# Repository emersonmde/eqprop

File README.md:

# Analog equilibrium propagation — XOR prototype B.1

A two-hidden-node analog resistive network for learning XOR through equilibrium propagation. The circuit settles physically; a classic 5 V Arduino Nano will measure equilibria and update sixteen programmable resistances. **The PCB is routed and checked; Nano firmware and physical validation are not yet implemented/completed.**

Start every new session with [project state and next steps](docs/project-state.md). It records what exists, what remains, and where to find the design, fabrication, programming and debugging instructions.

## Working files

- [Native KiCad project](cad/eqprop-xor/eqprop-xor.kicad_pro), including its child sheets and local libraries.
- [Design rationale and datasheets](docs/design.md), [component/pin tables](docs/kicad/00-overview.md), [preferred-parts BOM](docs/bom-pcbway.csv).
- [PCBWay fabrication and assembly](docs/fabrication.md).
- [Nano firmware contract](docs/firmware.md), [bench bring-up](docs/bring-up.md), [demo operation](docs/operation.md).
- [Engineering review](docs/ee-review.md), [validation evidence](docs/validation/).

## Simulation and release checks

From the repository root, using Python 3 and a virtual environment:

```sh
python3 -m venv .venv
source .venv/bin/activate
python -m pip install -r sim/requirements.txt
PYTHONPATH=sim python -m pytest sim/tests -q
PYTHONPATH=sim python -m eqprop.xor
python tools/generate_bom.py
python tools/export_manufacturing.py
```

Install ngspice for the SPICE tests; those tests skip when it is absent, so skipped tests do not constitute a complete release check. KiCad 9's `kicad-cli` is required for manufacturing export. The script discovers PATH or the standard macOS install; `--kicad-cli` can specify another executable. Generated fabrication files go in ignored `build/manufacturing/`. Save the exact approved release with the PCBWay order records when an order is placed.

The regression suite checks KCL, gradients, training, quantization, SPICE behavior and BOM consistency. These are retained because later hardware/firmware changes need them. Nominal DC models do not prove stability, noise, component spread or online finite-tap learning.

## Papers and Attribution

This project is a from-scratch implementation of techniques described in the following papers. No code was reused from any existing repository.

**Core algorithm:**
- Scellier & Bengio, ["Equilibrium Propagation: Bridging the Gap Between Energy-Based Models and Backpropagation"](https://arxiv.org/abs/1602.05179) (Frontiers in Computational Neuroscience, 2017) — the equilibrium propagation framework: free-phase settling, nudge-phase perturbation, and gradient extraction from energy differences.

**Analog hardware formulation:**
- Kendall et al., ["Training End-to-End Analog Neural Networks with Equilibrium Propagation"](https://arxiv.org/abs/2006.01981) (2020) — extends EqProp to nonlinear resistive networks. This project uses their conductance-space gradient formula (Theorem 1: `dC/dG = (dV_nudge² - dV_free²) / (2β)`), their proof that antiparallel diode pairs are valid EqProp nonlinear elements (Theorem 2), and their XOR demonstration architecture (Figure 3, Appendix D.2) as a starting point. The complementary-input encoding and digital-weight-update pattern also follow their approach.

**Symmetric nudging:**
- Laborieux et al., ["Scaling Equilibrium Propagation to Deep ConvNets by Drastically Reducing its Computational Cost"](https://arxiv.org/abs/2006.03824) (ICLR 2021) — the symmetric nudge variant (both +β and -β) used in the training loop to cancel gradient estimation bias.

**Referenced in the hardware design upgrade path:**
- Laborieux & Zenke, ["Holomorphic Equilibrium Propagation Computes Exact Gradients Through Finite Size Oscillations"](https://arxiv.org/abs/2209.00530) (NeurIPS 2022) — oscillating nudge + DFT-based gradient extraction for exact gradients without finite-β bias.

## License

Apache 2.0. See [LICENSE](LICENSE).

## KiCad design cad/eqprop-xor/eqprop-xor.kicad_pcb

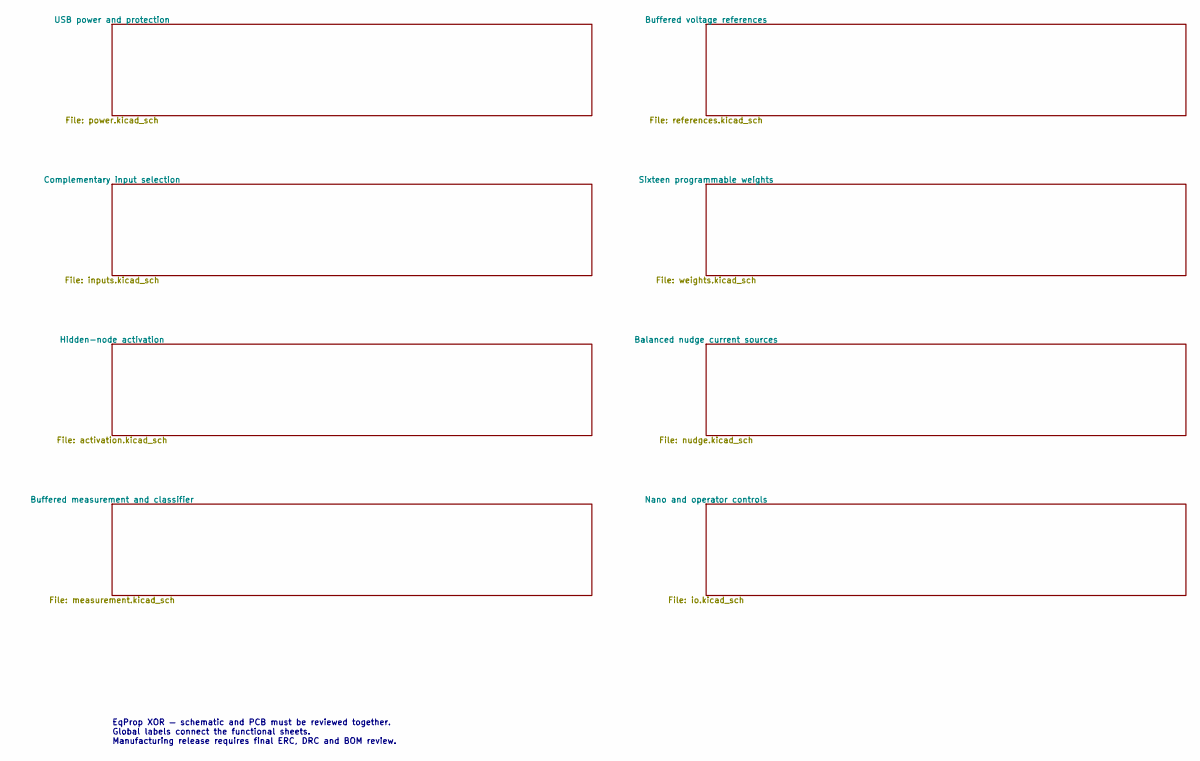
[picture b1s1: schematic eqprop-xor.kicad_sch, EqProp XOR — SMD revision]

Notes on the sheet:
EqProp XOR — schematic and PCB must be reviewed together. Global labels connect the functional sheets. Manufacturing release requires final ERC, DRC and BOM review.

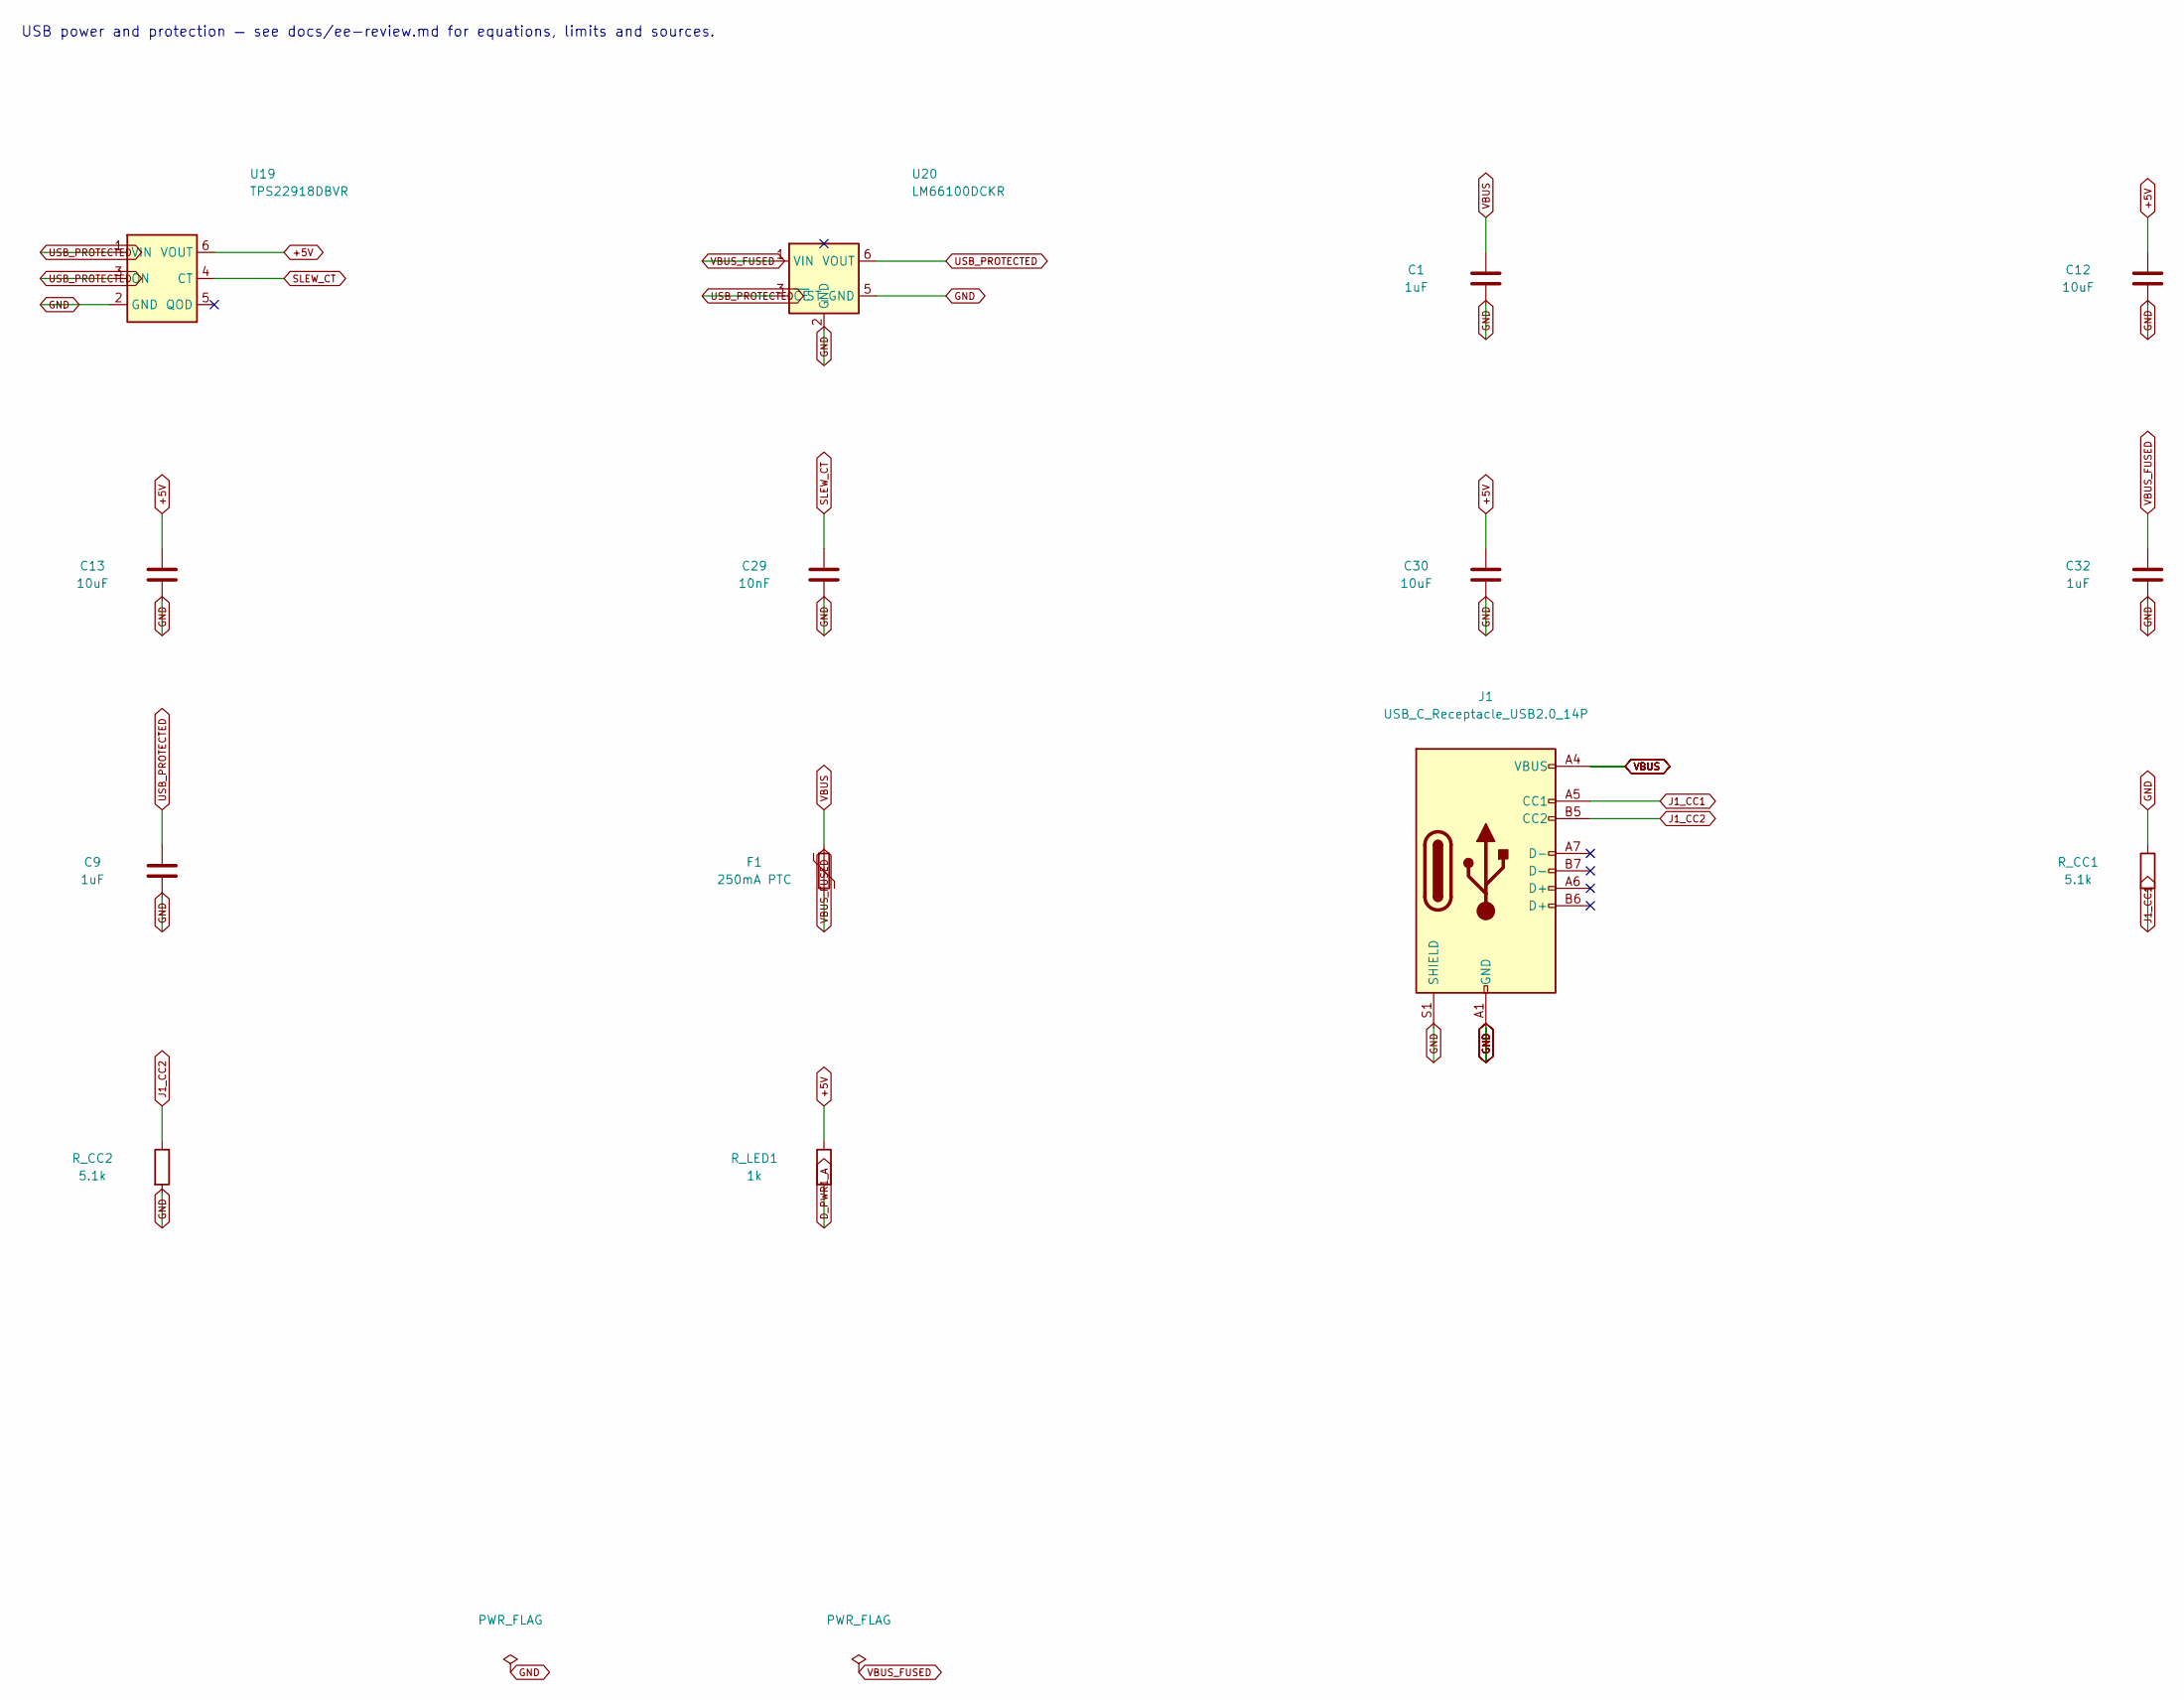
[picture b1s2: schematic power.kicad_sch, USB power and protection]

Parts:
C1, C9, C32: 1uF; C_0805_2012Metric; MPN C0805C105K4RACTU
C12, C13, C30: 10uF; C_0805_2012Metric; MPN C0805C106K8PACTU
C29: 10nF; C_0805_2012Metric; MPN C0805C103K5RACTU
F1: 250mA PTC; Fuse_1206_3216Metric; MPN MF-NSMF025X-2
J1: USB_C_Receptacle_USB2.0_14P; USB4085_Edge; MPN USB4085-GF-A
R_CC1, R_CC2: 5.1k; R_0805_2012Metric; Tolerance 1%; MPN CRCW08055K10FKEA
R_LED1: 1k; R_0805_2012Metric; Tolerance 1%; MPN CRCW08051K00FKEA
U19: TPS22918DBVR; SOT-23-6; MPN TPS22918DBVR
U20: LM66100DCKR; SOT-363_SC-70-6; MPN LM66100DCKR

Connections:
+5V: C12.1, C13.1, C30.1, R_LED1.1, U19.6 (VOUT); also elsewhere on the board
D_PWR1_A: R_LED1.2; also elsewhere on the board
GND: C1.2, C9.2, C12.2, C13.2, C29.2, C30.2, C32.2, J1.A1 (GND), J1.A12 (GND), J1.B1 (GND), J1.B12 (GND), J1.S1 (SHIELD), R_CC1.1, R_CC2.2, U19.2 (GND), U20.2 (GND), U20.5 (ST_GND); also elsewhere on the board
J1_CC1: J1.A5 (CC1), R_CC1.2
J1_CC2: J1.B5 (CC2), R_CC2.1
SLEW_CT: C29.1, U19.4 (CT)
USB_PROTECTED: C9.1, U19.1 (VIN), U19.3 (ON), U20.3 (~CE), U20.6 (VOUT)
VBUS: C1.1, F1.1, J1.A4 (VBUS), J1.A9 (VBUS), J1.B4 (VBUS), J1.B9 (VBUS)
VBUS_FUSED: C32.1, F1.2, U20.1 (VIN)

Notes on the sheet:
USB power and protection — see docs/ee-review.md for equations, limits and sources.

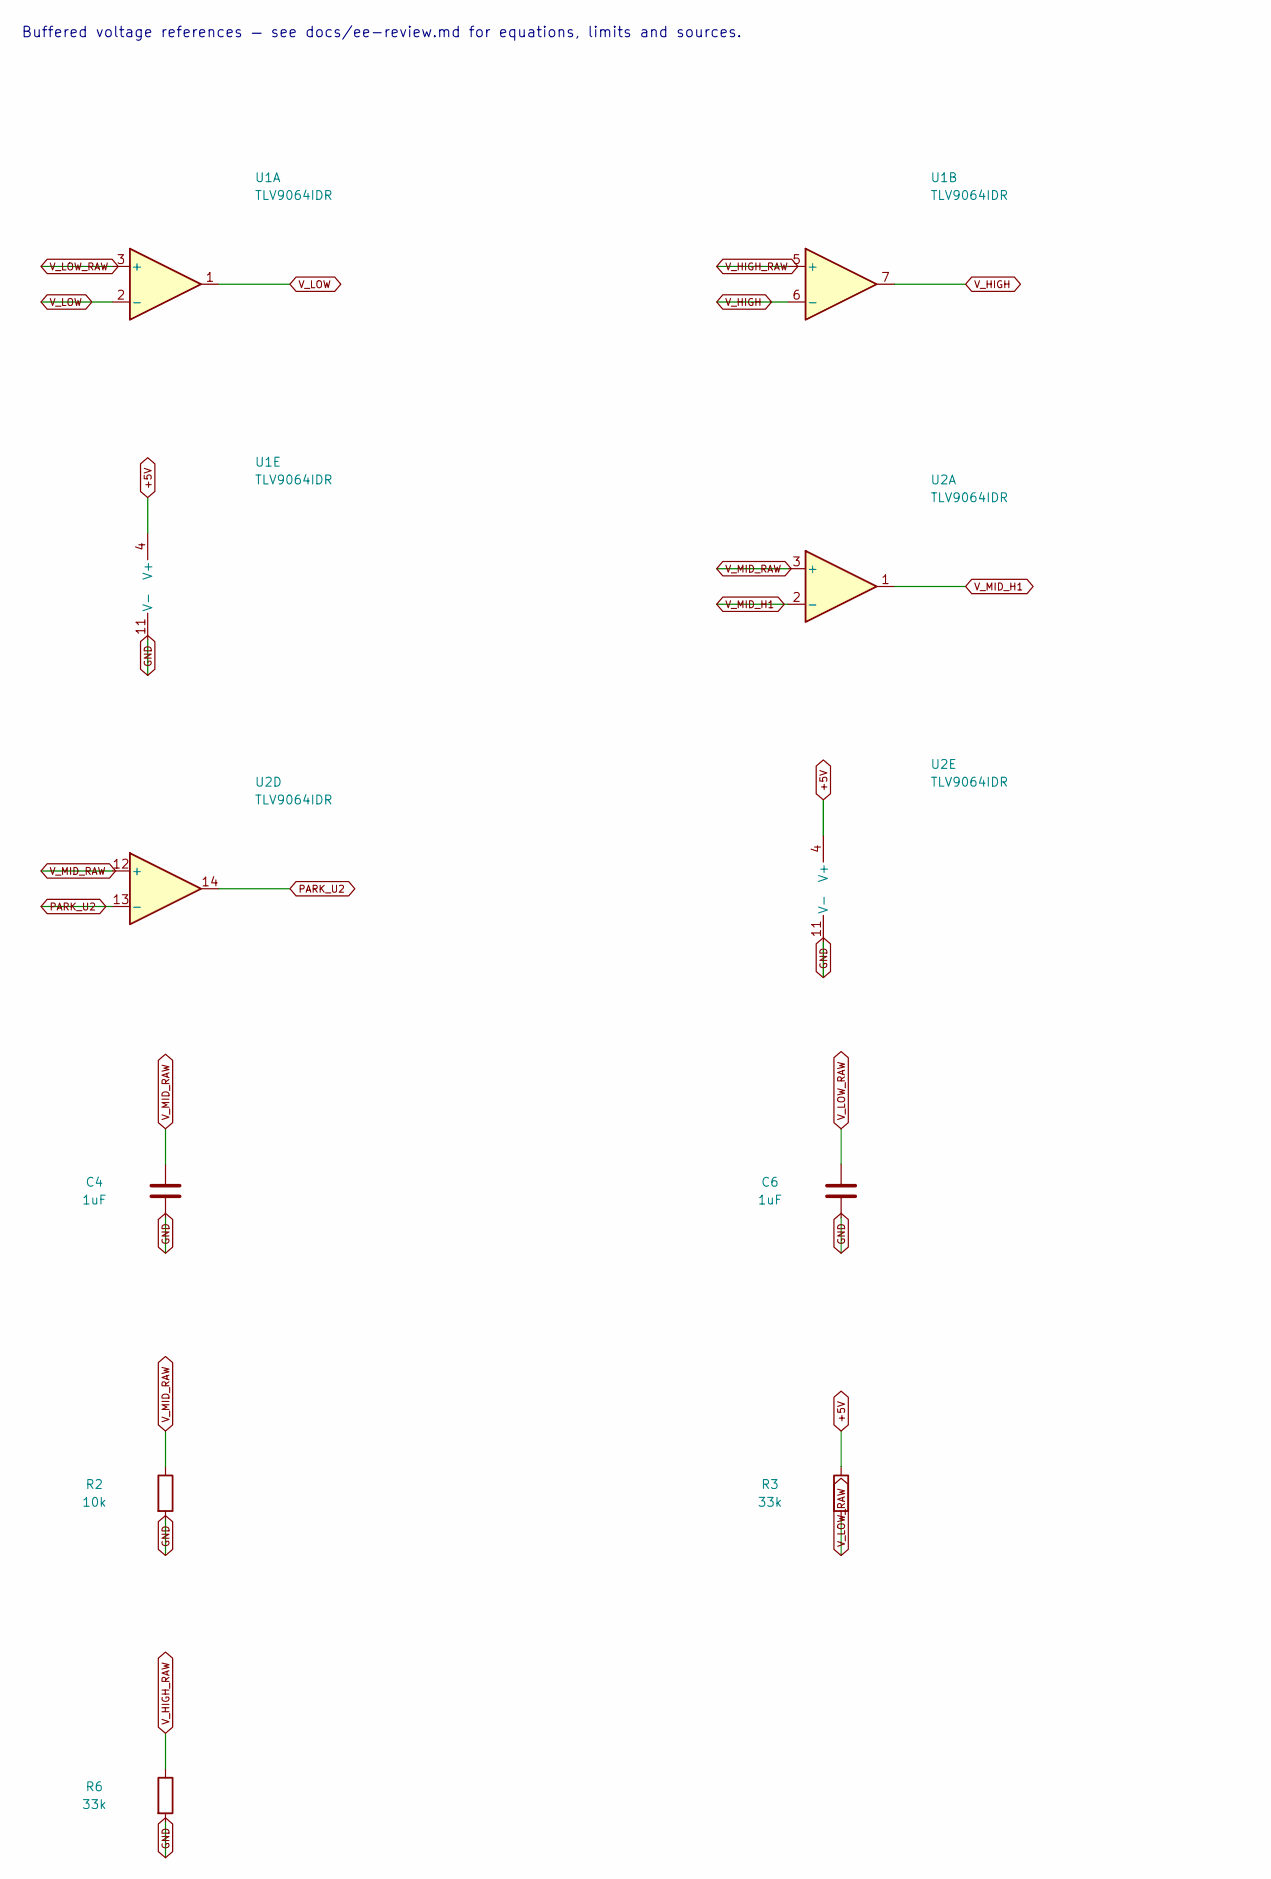
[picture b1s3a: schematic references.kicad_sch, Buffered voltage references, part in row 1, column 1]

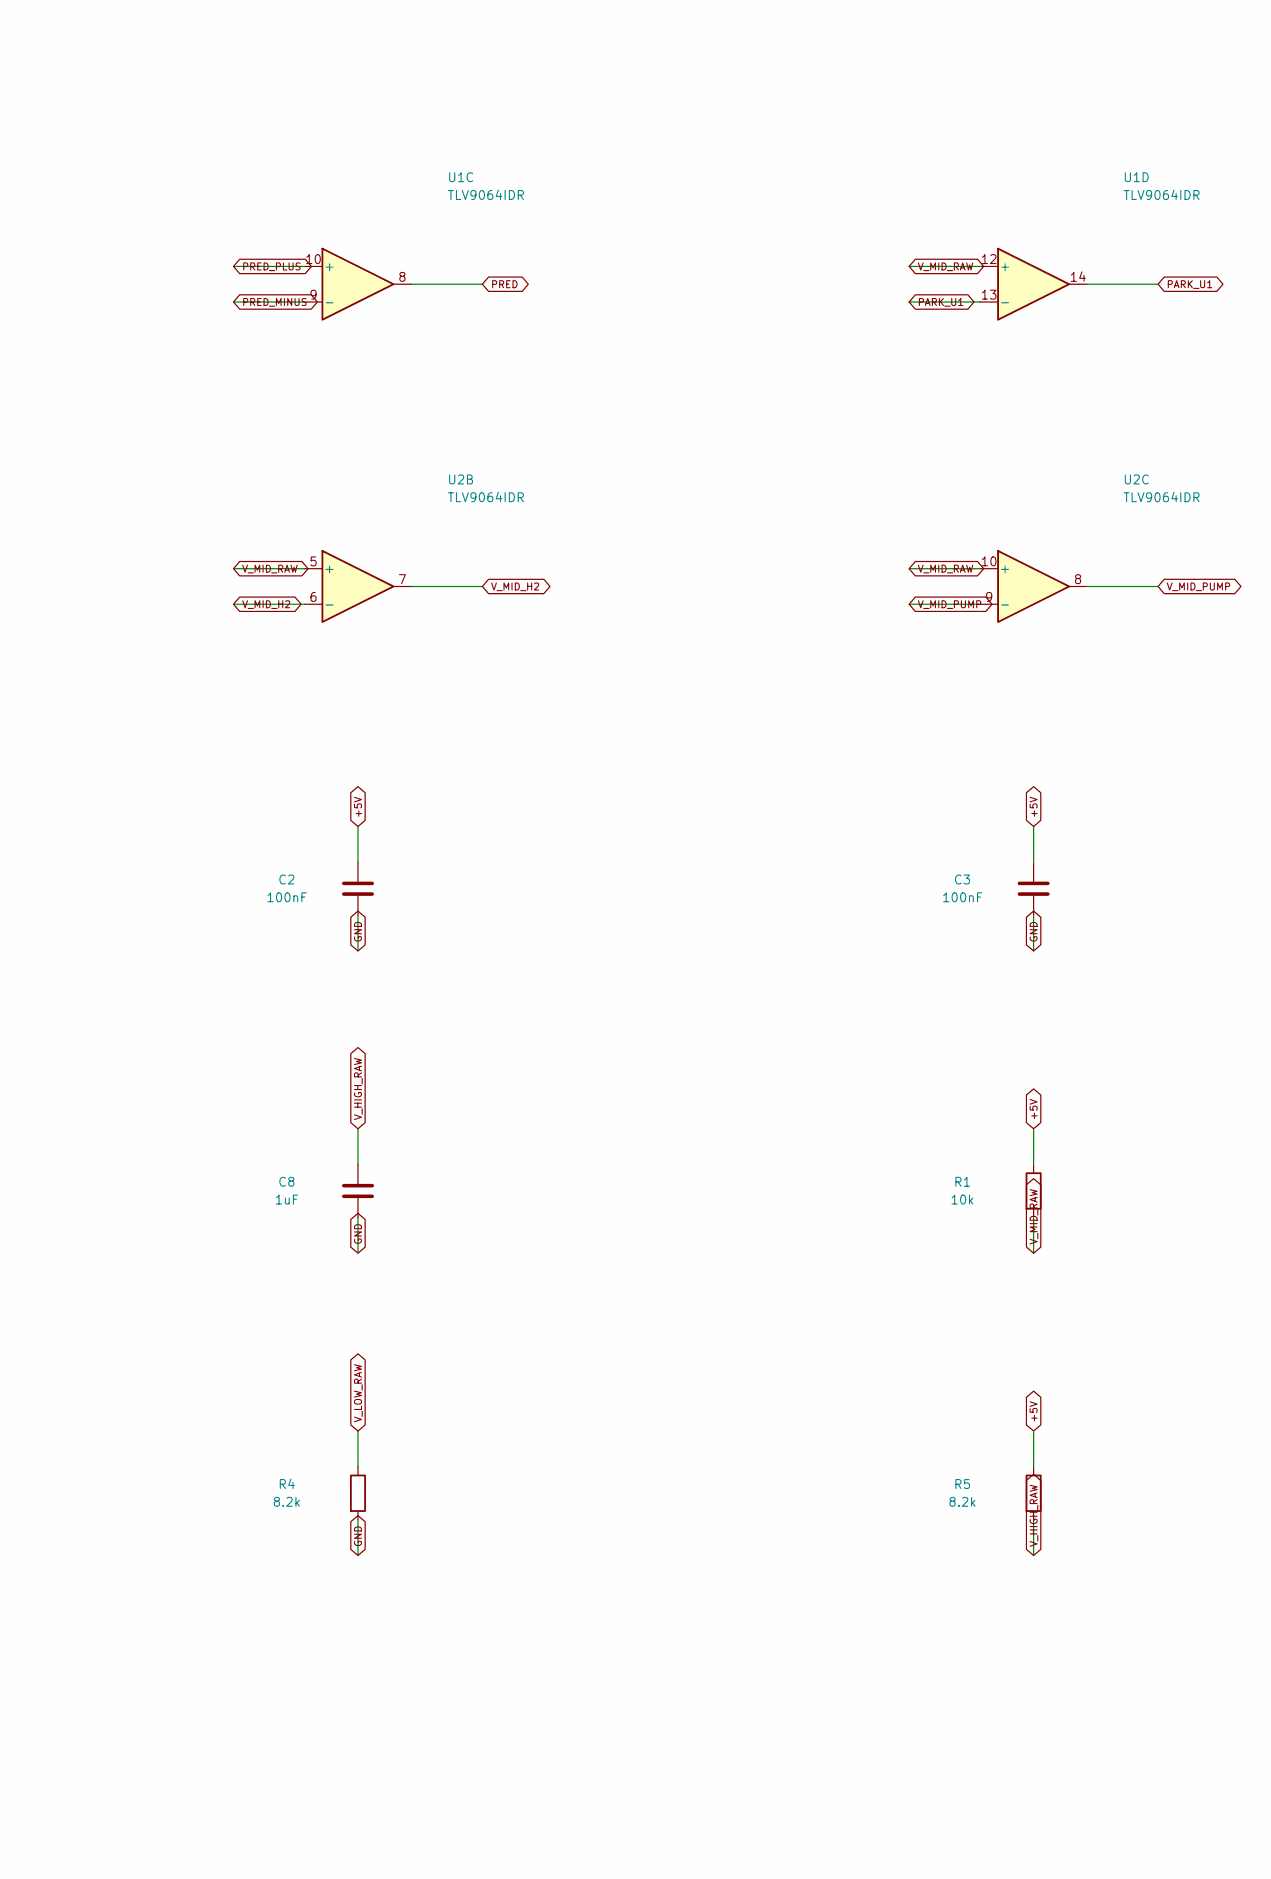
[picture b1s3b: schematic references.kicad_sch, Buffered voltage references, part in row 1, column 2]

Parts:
C2, C3: 100nF; C_0805_2012Metric; MPN C0805C104K5RACTU
C4, C6, C8: 1uF; C_0805_2012Metric; MPN C0805C105K4RACTU
R1, R2: 10k; R_0805_2012Metric; Tolerance 0.1%; MPN TNPW080510K0BEEA
R3, R6: 33k; R_0805_2012Metric; Tolerance 0.1%; MPN TNPW080533K0BEEA
R4, R5: 8.2k; R_0805_2012Metric; Tolerance 0.1%; MPN TNPW08058K20BEEA
U1, U2: TLV9064IDR; SOIC-14_3.9x8.7mm_P1.27mm; MPN TLV9064IDR

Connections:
+5V: C2.1, C3.1, R1.1, R3.1, R5.1, U1.4 (V+), U2.4 (V+); also elsewhere on the board
GND: C2.2, C3.2, C4.2, C6.2, C8.2, R2.2, R4.2, R6.2, U1.11 (V-), U2.11 (V-); also elsewhere on the board
PARK_U1: U1.13 (-), U1.14
PARK_U2: U2.13 (-), U2.14
PRED: U1.8; also elsewhere on the board
PRED_MINUS: U1.9 (-); also elsewhere on the board
PRED_PLUS: U1.10 (+); also elsewhere on the board
V_HIGH: U1.6 (-), U1.7; also elsewhere on the board
V_HIGH_RAW: C8.1, R5.2, R6.1, U1.5 (+)
V_LOW: U1.1, U1.2 (-); also elsewhere on the board
V_LOW_RAW: C6.1, R3.2, R4.1, U1.3 (+)
V_MID_H1: U2.1, U2.2 (-); also elsewhere on the board
V_MID_H2: U2.6 (-), U2.7; also elsewhere on the board
V_MID_PUMP: U2.8, U2.9 (-); also elsewhere on the board
V_MID_RAW: C4.1, R1.2, R2.1, U1.12 (+), U2.3 (+), U2.5 (+), U2.10 (+), U2.12 (+)

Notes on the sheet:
Buffered voltage references — see docs/ee-review.md for equations, limits and sources.

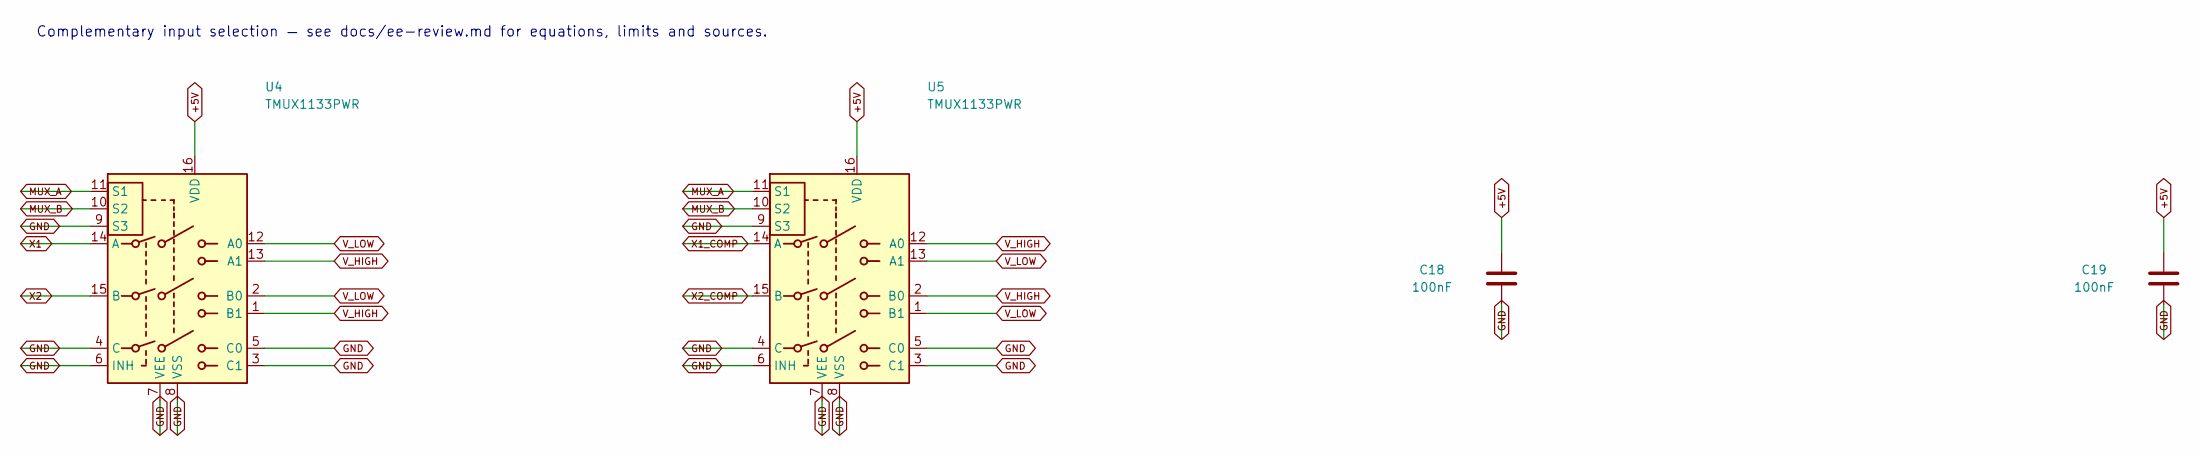
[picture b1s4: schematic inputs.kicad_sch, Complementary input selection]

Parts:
C18, C19: 100nF; C_0805_2012Metric; MPN C0805C104K5RACTU
U4, U5: TMUX1133PWR; TSSOP-16_4.4x5mm_P0.65mm; MPN TMUX1133PWR

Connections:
+5V: C18.1, C19.1, U4.16 (VDD), U5.16 (VDD); also elsewhere on the board
GND: C18.2, C19.2, U4.3 (C1), U4.4 (C), U4.5 (C0), U4.6 (INH), U4.7 (VEE), U4.8 (VSS), U4.9 (S3), U5.3 (C1), U5.4 (C), U5.5 (C0), U5.6 (INH), U5.7 (VEE), U5.8 (VSS), U5.9 (S3); also elsewhere on the board
MUX_A: U4.11 (S1), U5.11 (S1); also elsewhere on the board
MUX_B: U4.10 (S2), U5.10 (S2); also elsewhere on the board
V_HIGH: U4.1 (B1), U4.13 (A1), U5.2 (B0), U5.12 (A0); also elsewhere on the board
V_LOW: U4.2 (B0), U4.12 (A0), U5.1 (B1), U5.13 (A1); also elsewhere on the board
X1: U4.14 (A); also elsewhere on the board
X1_COMP: U5.14 (A); also elsewhere on the board
X2: U4.15 (B); also elsewhere on the board
X2_COMP: U5.15 (B); also elsewhere on the board

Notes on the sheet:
Complementary input selection — see docs/ee-review.md for equations, limits and sources.
